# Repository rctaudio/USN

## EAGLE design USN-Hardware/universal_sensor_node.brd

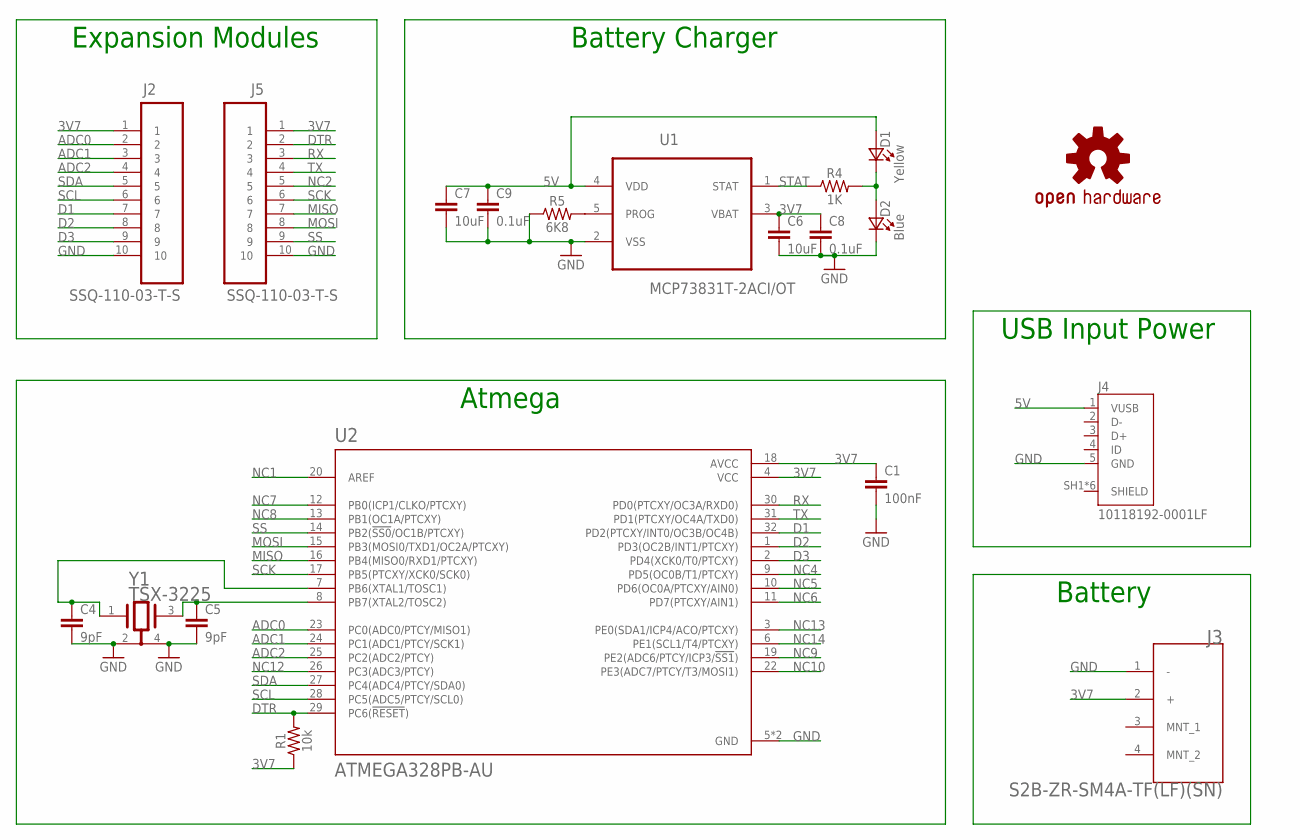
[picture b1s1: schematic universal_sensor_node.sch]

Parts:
C1: 100nF; 0603-CAP
C4, C5: 9pF; 0603-CAP
C6, C7: 10uF; 0603-CAP
C8, C9: 0.1uF; 0603-CAP
D1: Yellow; 0603
D2: Blue; 0603
J2, J5: SSQ-110-03-T-S; SAMTEC_SSQ-110-03-T-S
J3: JST_S2B-ZR-SM4A-TF_LF_SNJST_S2B-ZR-SM4A-TF_LF_SN_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; JST_S2B-ZR-SM4A-TF_LF_SN_0
J4: 10118192-0001LF; AMPHENOL_10118192-0001LF
LOGO1: OSHW-LOGOMINI; OSHW-LOGO-MINI
R1: 10k; 0603-RES
R4: 1K; 0603-RES
R5: 6K8; 0603-RES
U1: MCP73831T-2ACI/OT; SOT95P280X145-5N
U2: ATMEGA328PB-AU; QFP80P900X900X120-32N
Y1: TSX-3225EPSON_TSX-3225_16.0000MF09Z-AC3_0_0; TSX-3225

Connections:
3V7: C1.1, C6.1, C8.1, J2.1, J3.2 (+), J5.1, R1.1, U1.3 (VBAT), U2.4 (VCC), U2.18 (AVCC)
5V: C7.1, C9.1, D1.2 (A2), J4.1 (VUSB), U1.4 (VDD)
ADC0: J2.2, U2.23 (PC0(ADC0/PTCY/MISO1))
ADC1: J2.3, U2.24 (PC1(ADC1/PTCY/SCK1))
ADC2: J2.4, U2.25 (PC2(ADC2/PTCY))
D1: J2.7, U2.32 (PD2(PTCXY/INT0/OC3B/OC4B))
D2: J2.8, U2.1 (PD3(OC2B/INT1/PTCXY))
D3: J2.9, U2.2 (PD4(XCK0/T0/PTCXY))
DTR: J5.2, R1.2, U2.29 (PC6(!RESET!))
GND: C1.2, C4.2, C5.2, C6.2, C7.2, C8.2, C9.2, D2.1 (K2), J2.10, J3.1 (-), J4.5 (GND), J5.10, R5.1, U1.2 (VSS), U2.5 (GND), U2.21 (GND), Y1.2 (1_GND), Y1.4 (2_GND)
MISO: J5.7, U2.16 (PB4(MISO0/RXD1/PTCXY))
MOSI: J5.8, U2.15 (PB3(MOSI0/TXD1/OC2A/PTCXY))
unnamed: R5.2, U1.5 (PROG)
unnamed: D1.1 (K2), D2.2 (A2), R4.2
unnamed: C4.1, U2.7 (PB6(XTAL1/TOSC1)), Y1.1
unnamed: C5.1, U2.8 (PB7(XTAL2/TOSC2)), Y1.3
NC1: U2.20 (AREF)
NC2: J5.5
NC4: U2.9 (PD5(OC0B/T1/PTCXY))
NC5: U2.10 (PD6(OC0A/PTCXY/AIN0))
NC6: U2.11 (PD7(PTCXY/AIN1))
NC7: U2.12 (PB0(ICP1/CLKO/PTCXY))
NC8: U2.13 (PB1(OC1A/PTCXY))
NC9: U2.19 (PE2(ADC6/PTCY/ICP3/!SS1!))
NC10: U2.22 (PE3(ADC7/PTCY/T3/MOSI1))
NC12: U2.26 (PC3(ADC3/PTCY))
NC13: U2.3 (PE0(SDA1/ICP4/ACO/PTCXY))
NC14: U2.6 (PE1(SCL1/T4/PTCXY))
RX: J5.3, U2.30 (PD0(PTCXY/OC3A/RXD0))
SCK: J5.6, U2.17 (PB5(PTCXY/XCK0/SCK0))
SCL: J2.6, U2.28 (PC5(ADC5/PTCY/SCL0))
SDA: J2.5, U2.27 (PC4(ADC4/PTCY/SDA0))
SS: J5.9, U2.14 (PB2(!SS0!/OC1B/PTCXY))
STAT: R4.1, U1.1 (STAT)
TX: J5.4, U2.31 (PD1(PTCXY/OC4A/TXD0))

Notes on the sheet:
Atmega
Expansion Modules
Battery Charger
USB Input Power
Battery

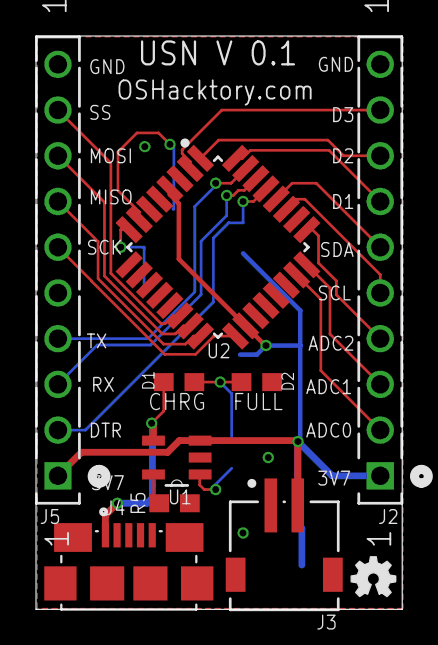
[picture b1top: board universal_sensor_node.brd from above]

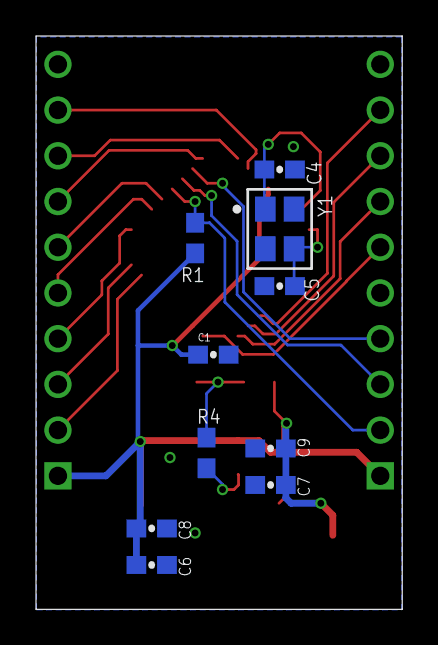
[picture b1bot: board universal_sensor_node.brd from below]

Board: 2 copper layers, 20.3 x 31.9 mm, 20 parts (10 on the bottom side), 23 nets.

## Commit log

2019-09-17 renamed board files. copied project over.
2019-09-17 moved folder structure again.
2019-09-17 forgot the eagle project file
2019-09-18 converting all parts into schematic library.
2019-09-19 finished with atmega components transfer.
2019-09-19 copied all all schematic components to project library. Cleaned up schematic.
2019-09-20 schematic capture done, board layout done, and everything is routed.
2019-09-20 looks good to me. Placed order with oshpark
2019-09-20 updated parts attributes for bom.
2019-09-20 added in digikey part number into library and updated parts.

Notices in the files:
parts and their libraries:
SparkFun-Aesthetics: Licensing: Creative Commons ShareAlike 4.0 International - https://creativecommons.org/licenses/by-sa/4.0
